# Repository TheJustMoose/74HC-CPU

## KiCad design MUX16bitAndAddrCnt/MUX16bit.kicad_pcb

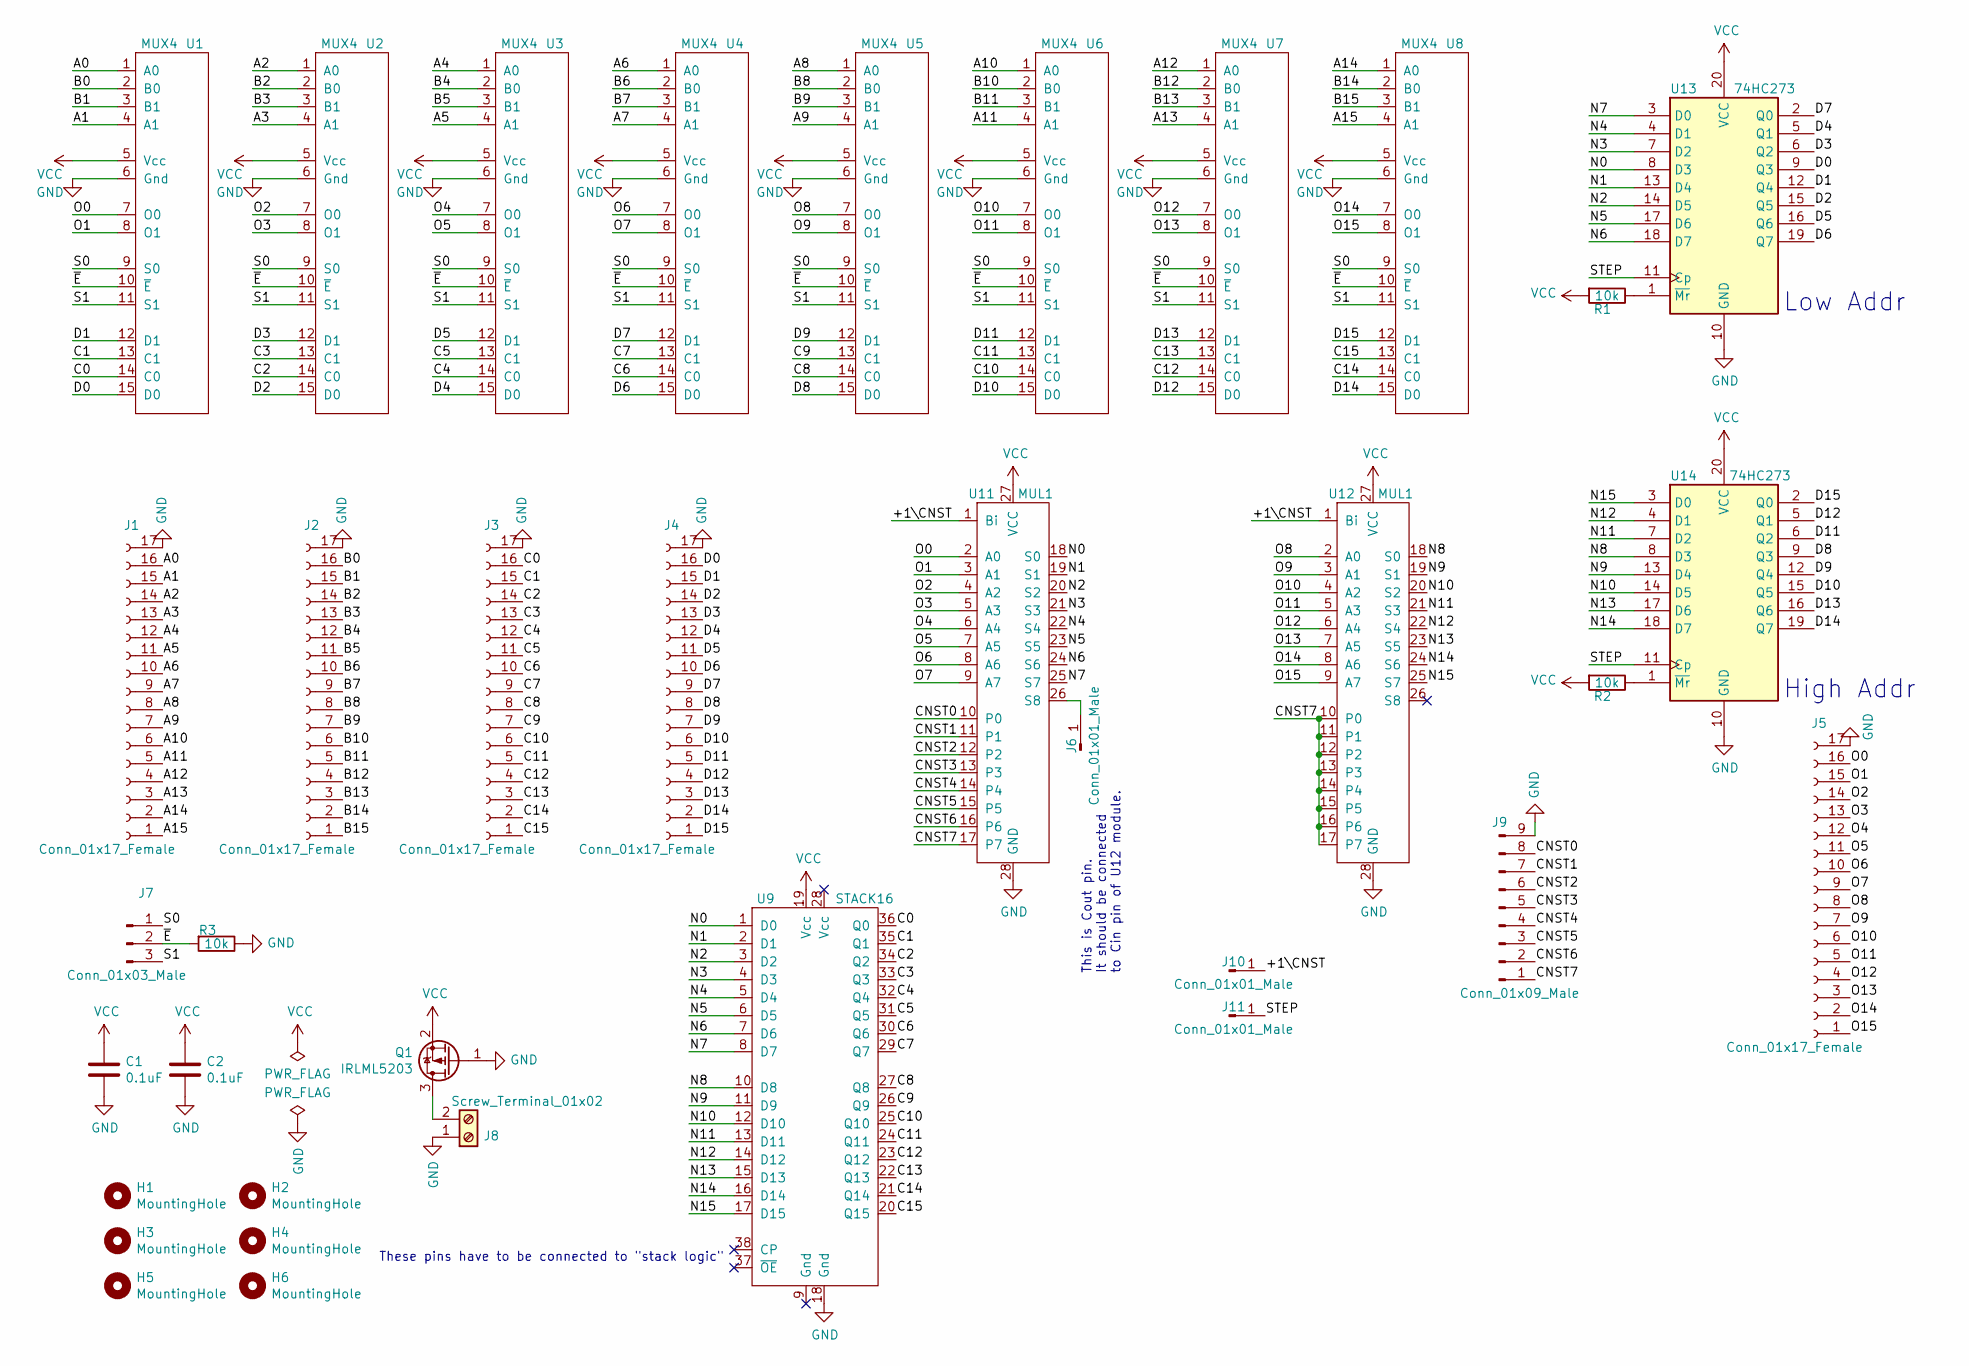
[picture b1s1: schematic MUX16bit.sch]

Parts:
C1, C2: 0.1uF; C_0805_2012Metric_Pad1.18x1.45mm_HandSolder
H1, H2, H3, H4, H5, H6: MountingHole; MountingHole_3.2mm_M3
J1, J2, J3, J4, J5: Conn_01x17_Female; PinSocket_1x17_P2.54mm_Vertical
J6, J10, J11: Conn_01x01_Male; PinHeader_1x01_P2.54mm_Vertical
J7: Conn_01x03_Male; PinHeader_1x03_P2.54mm_Vertical
J8: Screw_Terminal_01x02; TerminalBlock_Phoenix_PT-1,5-2-5.0-H_1x02_P5.00mm_Horizontal
J9: Conn_01x09_Male; PinHeader_1x09_P2.54mm_Vertical
Q1: IRLML5203; SOT-23
R1, R2, R3: 10k; R_0805_2012Metric_Pad1.20x1.40mm_HandSolder
U1, U2, U3, U4, U5, U6, U7, U8: MUX4; MUX1
U9: STACK16
U11, U12: MUL1
U13, U14: 74HC273; DIP-20_W7.62mm

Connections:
/+1\CNST: J10.1, U11.1 (Bi), U12.1 (Bi)
/A0: J1.16, U1.1 (A0)
/A1: J1.15, U1.4 (A1)
/A2: J1.14, U2.1 (A0)
/A3: J1.13, U2.4 (A1)
/A4: J1.12, U3.1 (A0)
/A5: J1.11, U3.4 (A1)
/A6: J1.10, U4.1 (A0)
/A7: J1.9, U4.4 (A1)
/A8: J1.8, U5.1 (A0)
/A9: J1.7, U5.4 (A1)
/A10: J1.6, U6.1 (A0)
/A11: J1.5, U6.4 (A1)
/A12: J1.4, U7.1 (A0)
/A13: J1.3, U7.4 (A1)
/A14: J1.2, U8.1 (A0)
/A15: J1.1, U8.4 (A1)
/B0: J2.16, U1.2 (B0)
/B1: J2.15, U1.3 (B1)
/B2: J2.14, U2.2 (B0)
/B3: J2.13, U2.3 (B1)
/B4: J2.12, U3.2 (B0)
/B5: J2.11, U3.3 (B1)
/B6: J2.10, U4.2 (B0)
/B7: J2.9, U4.3 (B1)
/B8: J2.8, U5.2 (B0)
/B9: J2.7, U5.3 (B1)
/B10: J2.6, U6.2 (B0)
/B11: J2.5, U6.3 (B1)
/B12: J2.4, U7.2 (B0)
/B13: J2.3, U7.3 (B1)
/B14: J2.2, U8.2 (B0)
/B15: J2.1, U8.3 (B1)
/C0: J3.16, U1.14 (C0), U9.36 (Q0)
/C1: J3.15, U1.13 (C1), U9.35 (Q1)
/C2: J3.14, U2.14 (C0), U9.34 (Q2)
/C3: J3.13, U2.13 (C1), U9.33 (Q3)
/C4: J3.12, U3.14 (C0), U9.32 (Q4)
/C5: J3.11, U3.13 (C1), U9.31 (Q5)
/C6: J3.10, U4.14 (C0), U9.30 (Q6)
/C7: J3.9, U4.13 (C1), U9.29 (Q7)
/C8: J3.8, U5.14 (C0), U9.27 (Q8)
/C9: J3.7, U5.13 (C1), U9.26 (Q9)
/C10: J3.6, U6.14 (C0), U9.25 (Q10)
/C11: J3.5, U6.13 (C1), U9.24 (Q11)
/C12: J3.4, U7.14 (C0), U9.23 (Q12)
/C13: J3.3, U7.13 (C1), U9.22 (Q13)
/C14: J3.2, U8.14 (C0), U9.21 (Q14)
/C15: J3.1, U8.13 (C1), U9.20 (Q15)
/CNST0: J9.8, U11.10 (P0)
/CNST1: J9.7, U11.11 (P1)
/CNST2: J9.6, U11.12 (P2)
/CNST3: J9.5, U11.13 (P3)
/CNST4: J9.4, U11.14 (P4)
/CNST5: J9.3, U11.15 (P5)
/CNST6: J9.2, U11.16 (P6)
/CNST7: J9.1, U11.17 (P7), U12.10 (P0), U12.11 (P1), U12.12 (P2), U12.13 (P3), U12.14 (P4), U12.15 (P5), U12.16 (P6), U12.17 (P7)
/D0: J4.16, U1.15 (D0), U13.9 (Q3)
/D1: J4.15, U1.12 (D1), U13.12 (Q4)
/D2: J4.14, U2.15 (D0), U13.15 (Q5)
/D3: J4.13, U2.12 (D1), U13.6 (Q2)
/D4: J4.12, U3.15 (D0), U13.5 (Q1)
/D5: J4.11, U3.12 (D1), U13.16 (Q6)
/D6: J4.10, U4.15 (D0), U13.19 (Q7)
/D7: J4.9, U4.12 (D1), U13.2 (Q0)
/D8: J4.8, U5.15 (D0), U14.9 (Q3)
/D9: J4.7, U5.12 (D1), U14.12 (Q4)
/D10: J4.6, U6.15 (D0), U14.15 (Q5)
/D11: J4.5, U6.12 (D1), U14.6 (Q2)
/D12: J4.4, U7.15 (D0), U14.5 (Q1)
/D13: J4.3, U7.12 (D1), U14.16 (Q6)
/D14: J4.2, U8.15 (D0), U14.19 (Q7)
/D15: J4.1, U8.12 (D1), U14.2 (Q0)
/N0: U9.1 (D0), U11.18 (S0), U13.8 (D3)
/N1: U9.2 (D1), U11.19 (S1), U13.13 (D4)
/N2: U9.3 (D2), U11.20 (S2), U13.14 (D5)
/N3: U9.4 (D3), U11.21 (S3), U13.7 (D2)
/N4: U9.5 (D4), U11.22 (S4), U13.4 (D1)
/N5: U9.6 (D5), U11.23 (S5), U13.17 (D6)
/N6: U9.7 (D6), U11.24 (S6), U13.18 (D7)
/N7: U9.8 (D7), U11.25 (S7), U13.3 (D0)
/N8: U9.10 (D8), U12.18 (S0), U14.8 (D3)
/N9: U9.11 (D9), U12.19 (S1), U14.13 (D4)
/N10: U9.12 (D10), U12.20 (S2), U14.14 (D5)
/N11: U9.13 (D11), U12.21 (S3), U14.7 (D2)
/N12: U9.14 (D12), U12.22 (S4), U14.4 (D1)
/N13: U9.15 (D13), U12.23 (S5), U14.17 (D6)
/N14: U9.16 (D14), U12.24 (S6), U14.18 (D7)
/N15: U9.17 (D15), U12.25 (S7), U14.3 (D0)
/O0: J5.16, U1.7 (O0), U11.2 (A0)
/O1: J5.15, U1.8 (O1), U11.3 (A1)
/O2: J5.14, U2.7 (O0), U11.4 (A2)
/O3: J5.13, U2.8 (O1), U11.5 (A3)
/O4: J5.12, U3.7 (O0), U11.6 (A4)
/O5: J5.11, U3.8 (O1), U11.7 (A5)
/O6: J5.10, U4.7 (O0), U11.8 (A6)
/O7: J5.9, U4.8 (O1), U11.9 (A7)
/O8: J5.8, U5.7 (O0), U12.2 (A0)
/O9: J5.7, U5.8 (O1), U12.3 (A1)
/O10: J5.6, U6.7 (O0), U12.4 (A2)
/O11: J5.5, U6.8 (O1), U12.5 (A3)
/O12: J5.4, U7.7 (O0), U12.6 (A4)
/O13: J5.3, U7.8 (O1), U12.7 (A5)
/O14: J5.2, U8.7 (O0), U12.8 (A6)
/O15: J5.1, U8.8 (O1), U12.9 (A7)
/S0: J7.1, U1.9 (S0), U2.9 (S0), U3.9 (S0), U4.9 (S0), U5.9 (S0), U6.9 (S0), U7.9 (S0), U8.9 (S0)
/S1: J7.3, U1.11 (S1), U2.11 (S1), U3.11 (S1), U4.11 (S1), U5.11 (S1), U6.11 (S1), U7.11 (S1), U8.11 (S1)
/STEP: J11.1, U13.11 (Cp), U14.11 (Cp)
/~E: J7.2, R3.2, U1.10 (~E), U2.10 (~E), U3.10 (~E), U4.10 (~E), U5.10 (~E), U6.10 (~E), U7.10 (~E), U8.10 (~E)
GND: C1.2, C2.2, J1.17, J2.17, J3.17, J4.17, J5.17, J8.1, J9.9, Q1.1 (G), R3.1, U1.6 (Gnd), U2.6 (Gnd), U3.6 (Gnd), U4.6 (Gnd), U5.6 (Gnd), U6.6 (Gnd), U7.6 (Gnd), U8.6 (Gnd), U9.18 (Gnd), U11.28 (GND), U12.28 (GND), U13.10 (GND), U14.10 (GND)
unnamed: J6.1, U11.26 (S8)
unnamed: J8.2, Q1.3 (D)
unnamed: R1.1, U13.1 (~Mr)
unnamed: R2.1, U14.1 (~Mr)
VCC: C1.1, C2.1, Q1.2 (S), R1.2, R2.2, U1.5 (Vcc), U2.5 (Vcc), U3.5 (Vcc), U4.5 (Vcc), U5.5 (Vcc), U6.5 (Vcc), U7.5 (Vcc), U8.5 (Vcc), U9.19 (Vcc), U11.27 (VCC), U12.27 (VCC), U13.20 (VCC), U14.20 (VCC)

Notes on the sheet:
Low Addr
High Addr
This is Cout pin. It should be connected to Cin pin of U12 module.
These pins have to be connected to "stack logic"

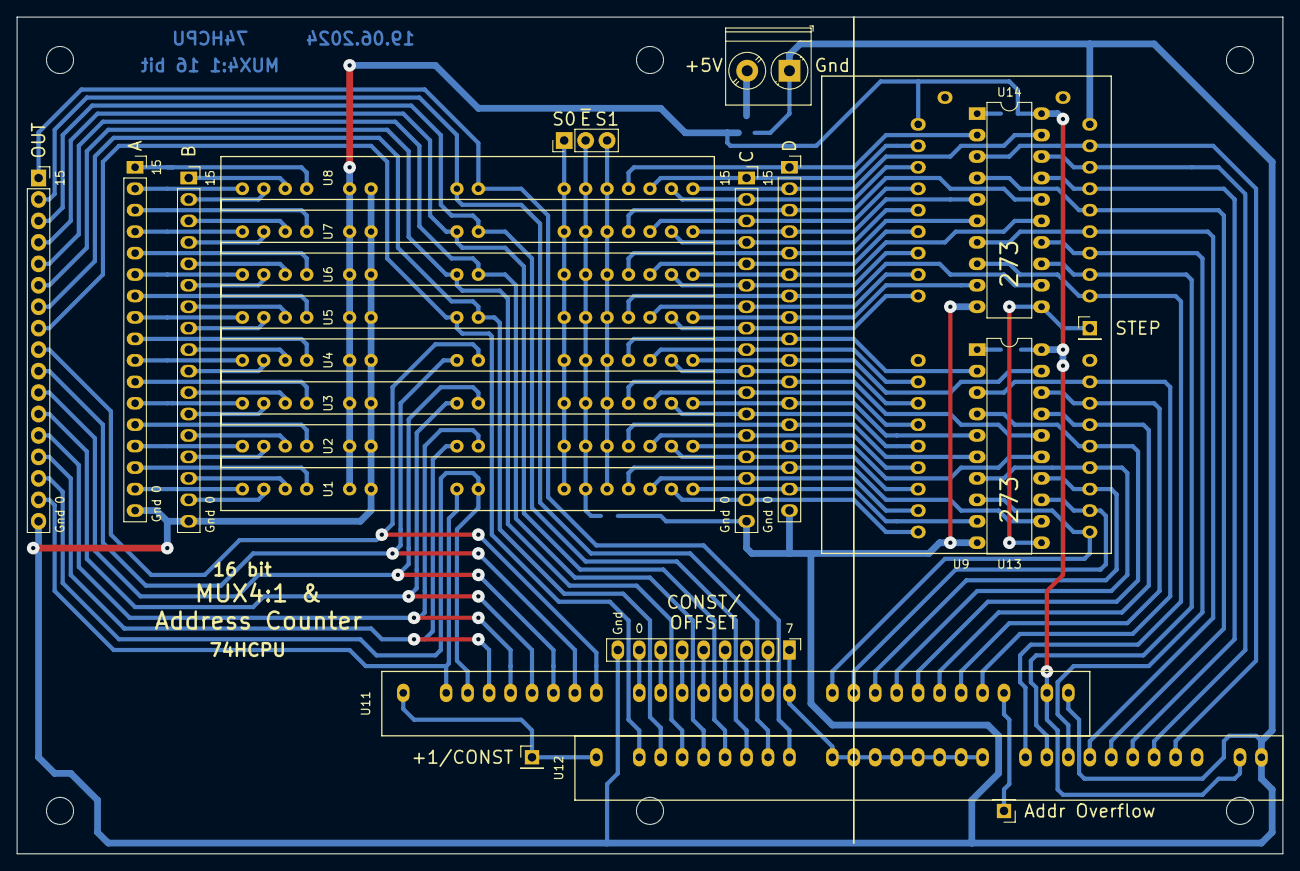
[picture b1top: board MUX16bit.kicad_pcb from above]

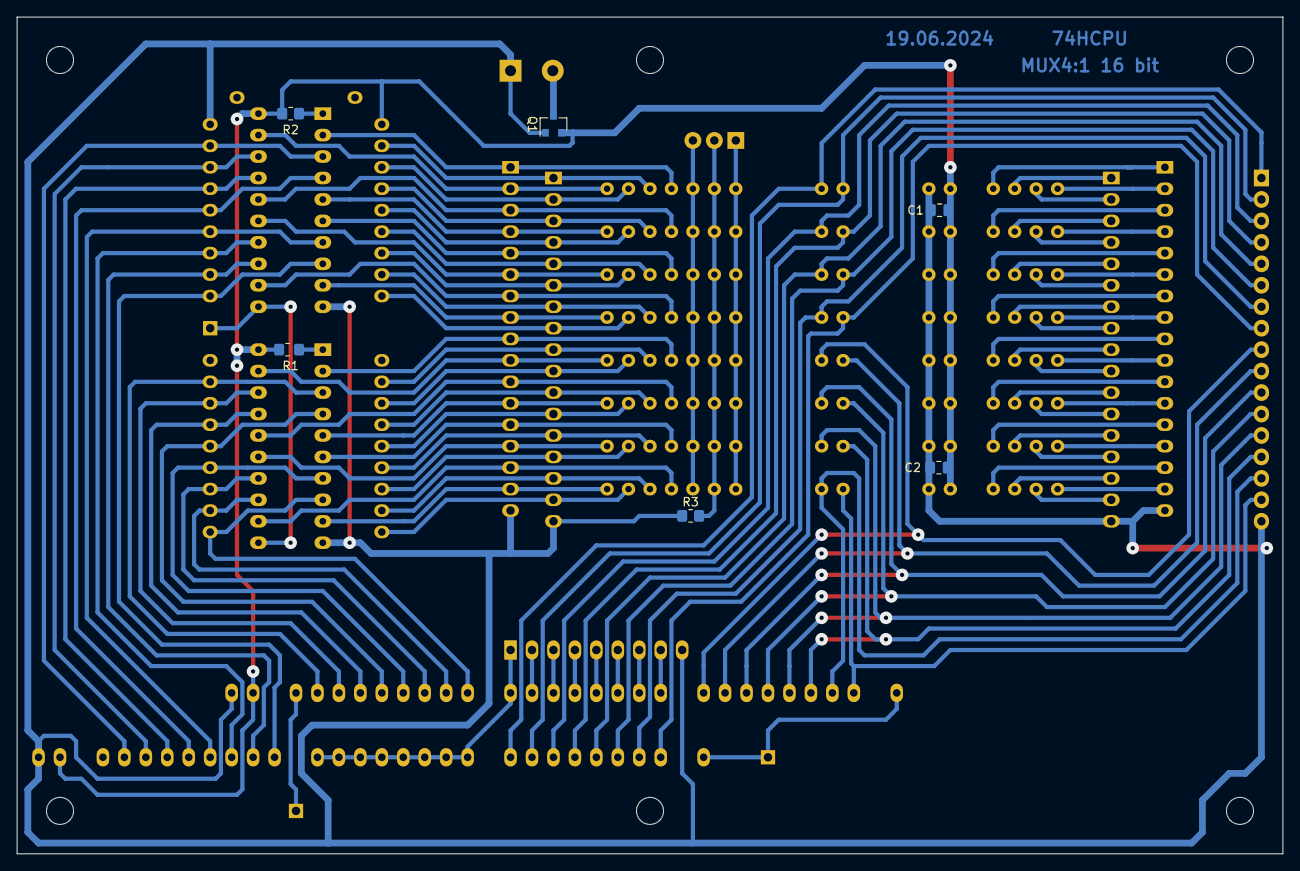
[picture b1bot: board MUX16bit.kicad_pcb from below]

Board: 2 copper layers, 149.9 x 99.1 mm, 36 parts (6 on the bottom side), 115 nets.

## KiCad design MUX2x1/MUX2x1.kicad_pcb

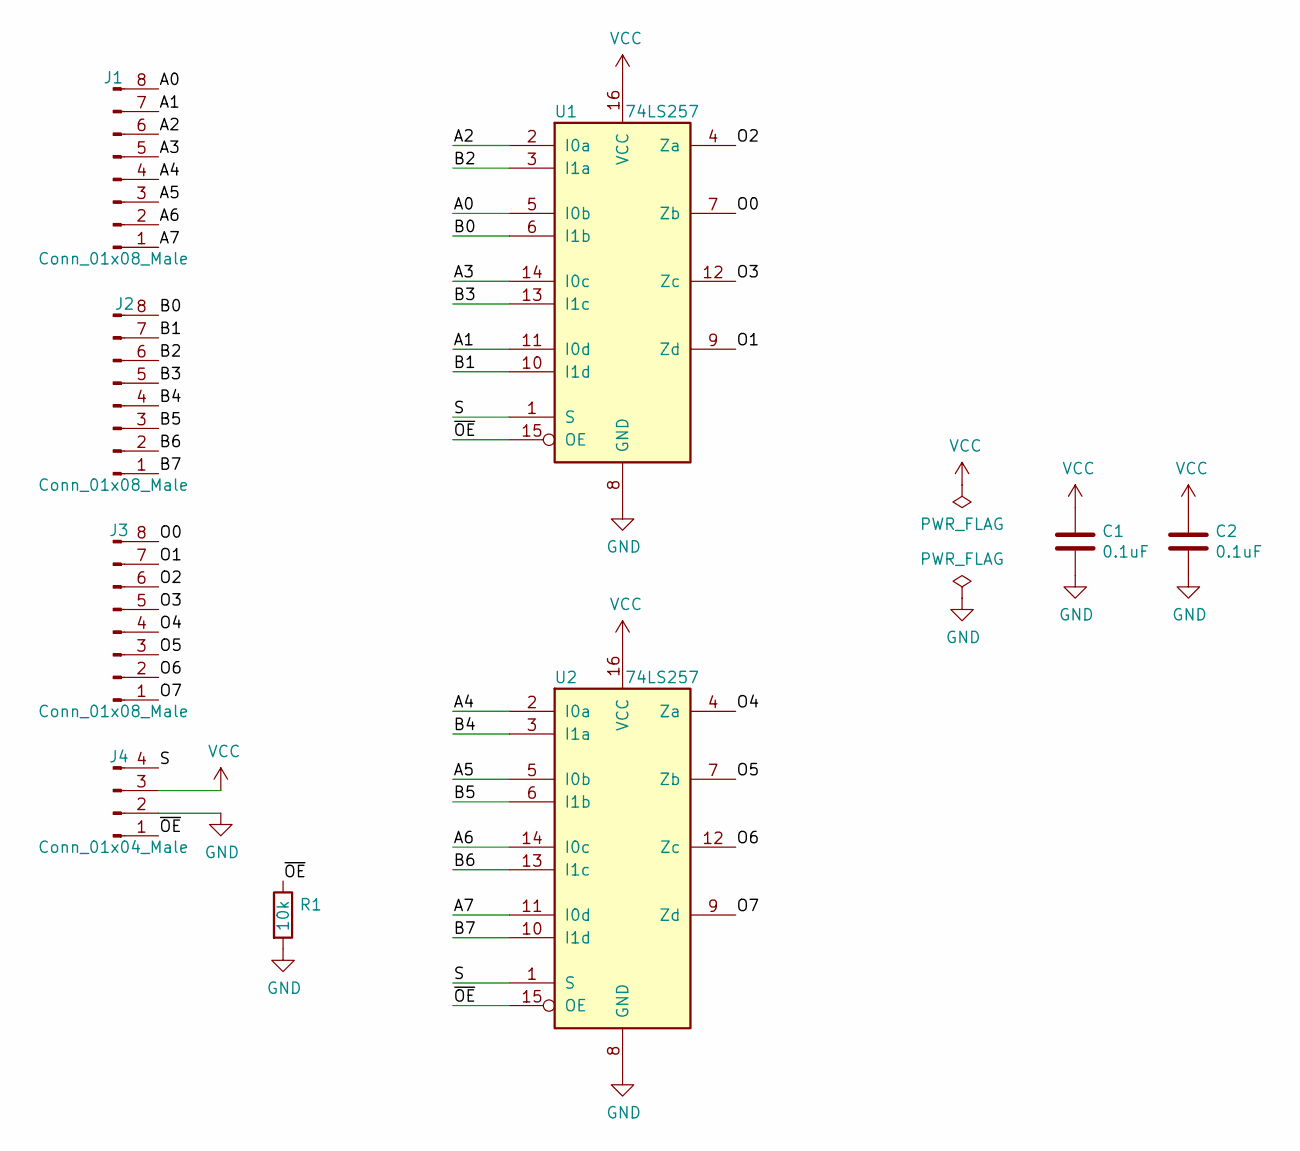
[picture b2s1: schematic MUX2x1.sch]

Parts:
C1, C2: 0.1uF; C_0805_2012Metric_Pad1.18x1.45mm_HandSolder
J1, J2, J3: Conn_01x08_Male; PinHeader_1x08_P2.54mm_Horizontal
J4: Conn_01x04_Male; PinHeader_1x04_P2.54mm_Horizontal
R1: 10k; R_0805_2012Metric_Pad1.20x1.40mm_HandSolder
U1, U2: 74LS257; DIP-16_W7.62mm_Socket

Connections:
/A0: J1.8, U1.5 (I0b)
/A1: J1.7, U1.11 (I0d)
/A2: J1.6, U1.2 (I0a)
/A3: J1.5, U1.14 (I0c)
/A4: J1.4, U2.2 (I0a)
/A5: J1.3, U2.5 (I0b)
/A6: J1.2, U2.14 (I0c)
/A7: J1.1, U2.11 (I0d)
/B0: J2.8, U1.6 (I1b)
/B1: J2.7, U1.10 (I1d)
/B2: J2.6, U1.3 (I1a)
/B3: J2.5, U1.13 (I1c)
/B4: J2.4, U2.3 (I1a)
/B5: J2.3, U2.6 (I1b)
/B6: J2.2, U2.13 (I1c)
/B7: J2.1, U2.10 (I1d)
/O0: J3.8, U1.7 (Zb)
/O1: J3.7, U1.9 (Zd)
/O2: J3.6, U1.4 (Za)
/O3: J3.5, U1.12 (Zc)
/O4: J3.4, U2.4 (Za)
/O5: J3.3, U2.7 (Zb)
/O6: J3.2, U2.12 (Zc)
/O7: J3.1, U2.9 (Zd)
/S: J4.4, U1.1 (S), U2.1 (S)
/~OE: J4.1, R1.1, U1.15 (OE), U2.15 (OE)
GND: C1.2, C2.2, J4.2, R1.2, U1.8 (GND), U2.8 (GND)
VCC: C1.1, C2.1, J4.3, U1.16 (VCC), U2.16 (VCC)

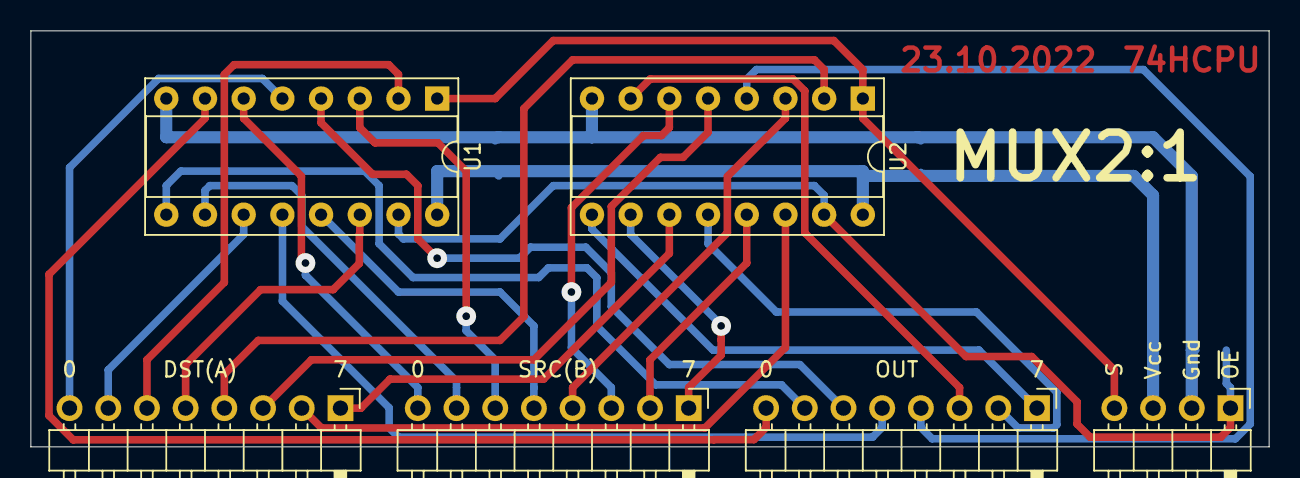
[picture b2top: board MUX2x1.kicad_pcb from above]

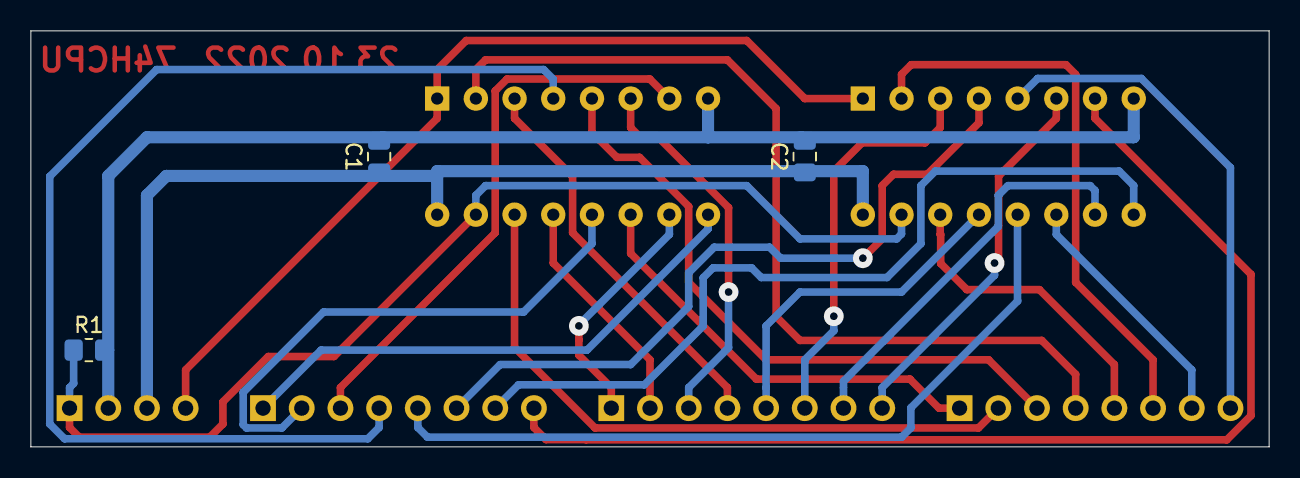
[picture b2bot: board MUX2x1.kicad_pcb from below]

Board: 2 copper layers, 81.3 x 27.3 mm, 9 parts (3 on the bottom side), 28 nets.

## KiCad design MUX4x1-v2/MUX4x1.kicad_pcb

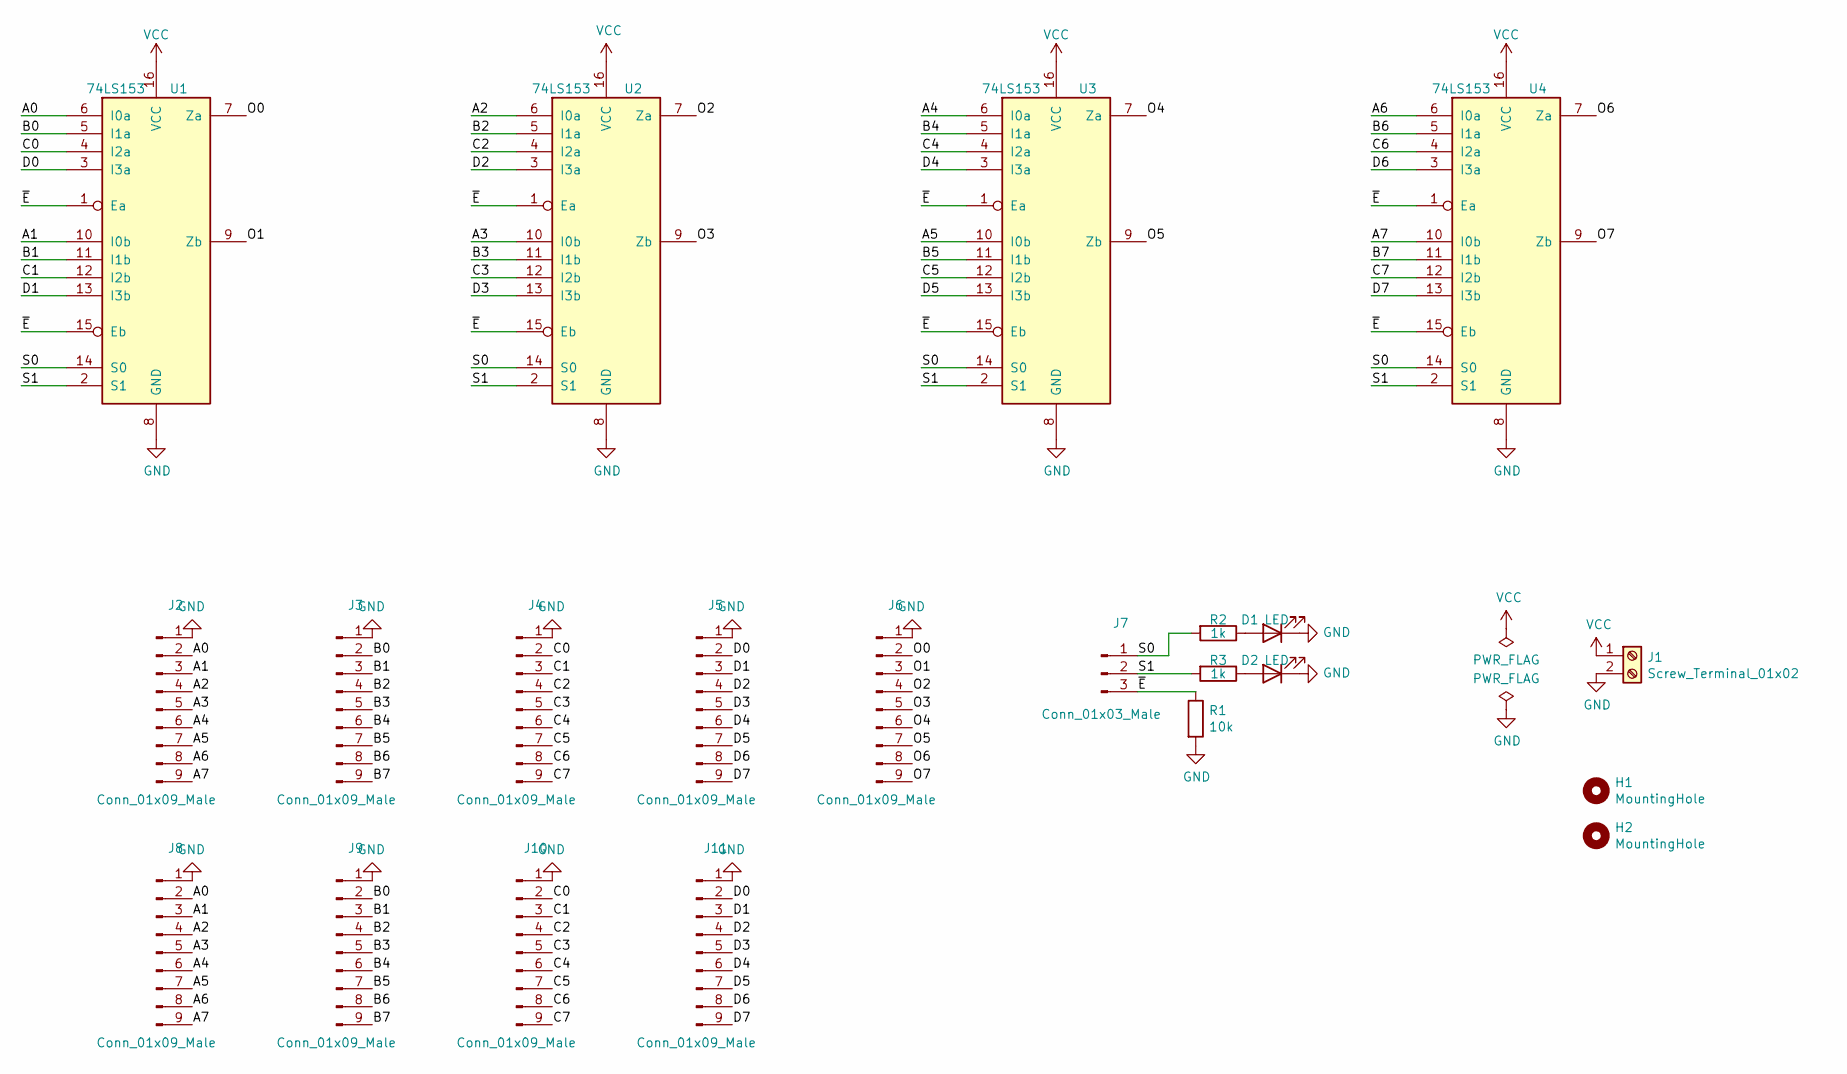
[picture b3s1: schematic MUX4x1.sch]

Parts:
D1, D2: LED; LED_0805_2012Metric_Pad1.15x1.40mm_HandSolder
H1, H2: MountingHole; MountingHole_3.2mm_M3
J1: Screw_Terminal_01x02; TerminalBlock_Phoenix_PT-1,5-2-5.0-H_1x02_P5.00mm_Horizontal
J2, J3, J4, J5, J6, J8, J9, J10, J11: Conn_01x09_Male; PinHeader_1x09_P2.54mm_Vertical
J7: Conn_01x03_Male; PinHeader_1x03_P2.54mm_Vertical
R1: 10k; R_0805_2012Metric_Pad1.20x1.40mm_HandSolder
R2, R3: 1k; R_0805_2012Metric_Pad1.20x1.40mm_HandSolder
U1, U2, U3, U4: 74LS153; DIP-16_W7.62mm_Socket

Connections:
/A0: J2.2, J8.2, U1.6 (I0a)
/A1: J2.3, J8.3, U1.10 (I0b)
/A2: J2.4, J8.4, U2.6 (I0a)
/A3: J2.5, J8.5, U2.10 (I0b)
/A4: J2.6, J8.6, U3.6 (I0a)
/A5: J2.7, J8.7, U3.10 (I0b)
/A6: J2.8, J8.8, U4.6 (I0a)
/A7: J2.9, J8.9, U4.10 (I0b)
/B0: J3.2, J9.2, U1.5 (I1a)
/B1: J3.3, J9.3, U1.11 (I1b)
/B2: J3.4, J9.4, U2.5 (I1a)
/B3: J3.5, J9.5, U2.11 (I1b)
/B4: J3.6, J9.6, U3.5 (I1a)
/B5: J3.7, J9.7, U3.11 (I1b)
/B6: J3.8, J9.8, U4.5 (I1a)
/B7: J3.9, J9.9, U4.11 (I1b)
/C0: J4.2, J10.2, U1.4 (I2a)
/C1: J4.3, J10.3, U1.12 (I2b)
/C2: J4.4, J10.4, U2.4 (I2a)
/C3: J4.5, J10.5, U2.12 (I2b)
/C4: J4.6, J10.6, U3.4 (I2a)
/C5: J4.7, J10.7, U3.12 (I2b)
/C6: J4.8, J10.8, U4.4 (I2a)
/C7: J4.9, J10.9, U4.12 (I2b)
/D0: J5.2, J11.2, U1.3 (I3a)
/D1: J5.3, J11.3, U1.13 (I3b)
/D2: J5.4, J11.4, U2.3 (I3a)
/D3: J5.5, J11.5, U2.13 (I3b)
/D4: J5.6, J11.6, U3.3 (I3a)
/D5: J5.7, J11.7, U3.13 (I3b)
/D6: J5.8, J11.8, U4.3 (I3a)
/D7: J5.9, J11.9, U4.13 (I3b)
/O0: J6.2, U1.7 (Za); also elsewhere on the board
/O1: J6.3, U1.9 (Zb); also elsewhere on the board
/O2: J6.4, U2.7 (Za); also elsewhere on the board
/O3: J6.5, U2.9 (Zb); also elsewhere on the board
/O4: J6.6, U3.7 (Za); also elsewhere on the board
/O5: J6.7, U3.9 (Zb); also elsewhere on the board
/O6: J6.8, U4.7 (Za); also elsewhere on the board
/O7: J6.9, U4.9 (Zb); also elsewhere on the board
/S0: J7.1, R2.2, U1.14 (S0), U2.14 (S0), U3.14 (S0), U4.14 (S0)
/S1: J7.2, R3.2, U1.2 (S1), U2.2 (S1), U3.2 (S1), U4.2 (S1)
/~E: J7.3, R1.1, U1.1 (Ea), U1.15 (Eb), U2.1 (Ea), U2.15 (Eb), U3.1 (Ea), U3.15 (Eb), U4.1 (Ea), U4.15 (Eb)
GND: D1.1 (K), D2.1 (K), J1.2, J2.1, J3.1, J4.1, J5.1, J6.1, J8.1, J9.1, J10.1, J11.1, R1.2, U1.8 (GND), U2.8 (GND), U3.8 (GND), U4.8 (GND); also elsewhere on the board
unnamed: D1.2 (A), R2.1
unnamed: D2.2 (A), R3.1
VCC: J1.1, U1.16 (VCC), U2.16 (VCC), U3.16 (VCC), U4.16 (VCC)

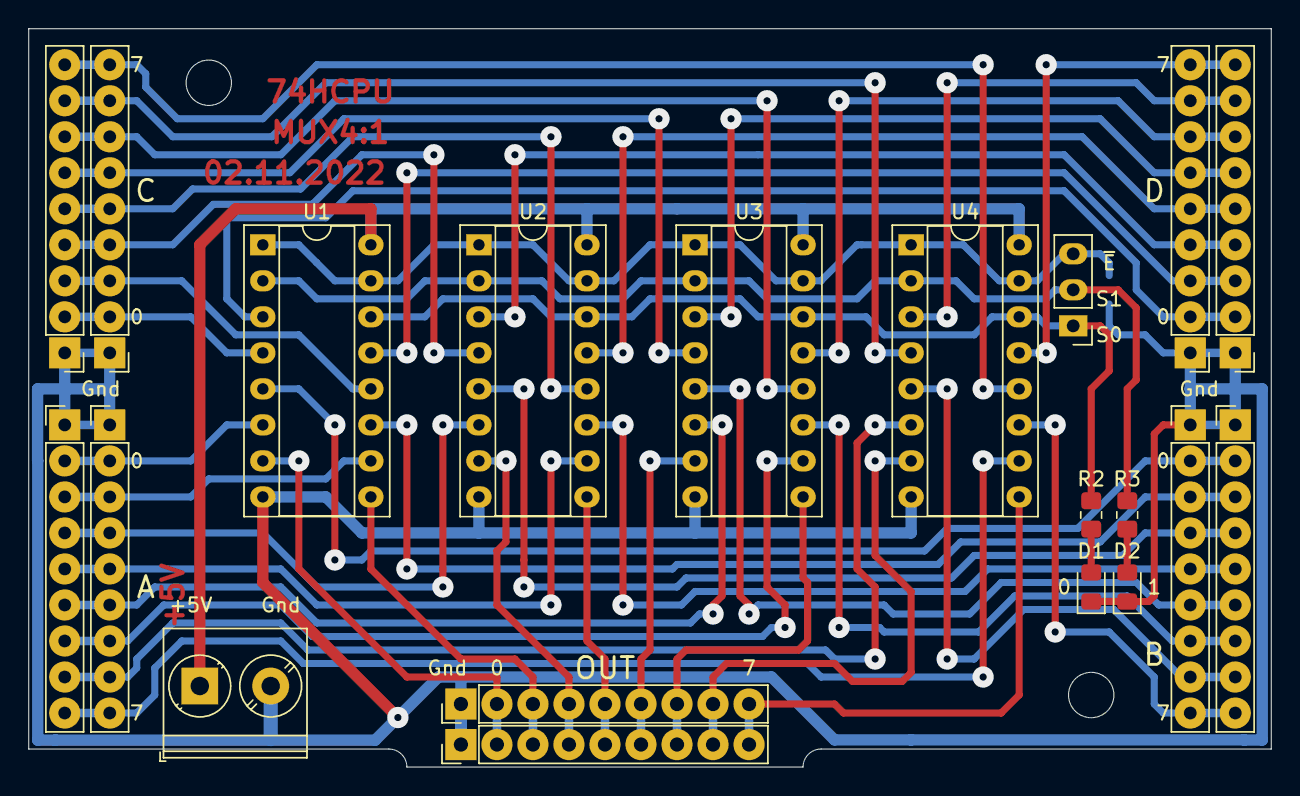
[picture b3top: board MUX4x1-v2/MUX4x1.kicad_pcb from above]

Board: 2 copper layers, 87.6 x 52.1 mm, 23 parts (1 on the bottom side), 47 nets.

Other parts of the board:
J12: Conn_01x09_Male; PinHeader_1x09_P2.54mm_Vertical

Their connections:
/O0: J12.2; also elsewhere on the board
/O1: J12.3; also elsewhere on the board
/O2: J12.4; also elsewhere on the board
/O3: J12.5; also elsewhere on the board
/O4: J12.6; also elsewhere on the board
/O5: J12.7; also elsewhere on the board
/O6: J12.8; also elsewhere on the board
/O7: J12.9; also elsewhere on the board
GND: J12.1; also elsewhere on the board

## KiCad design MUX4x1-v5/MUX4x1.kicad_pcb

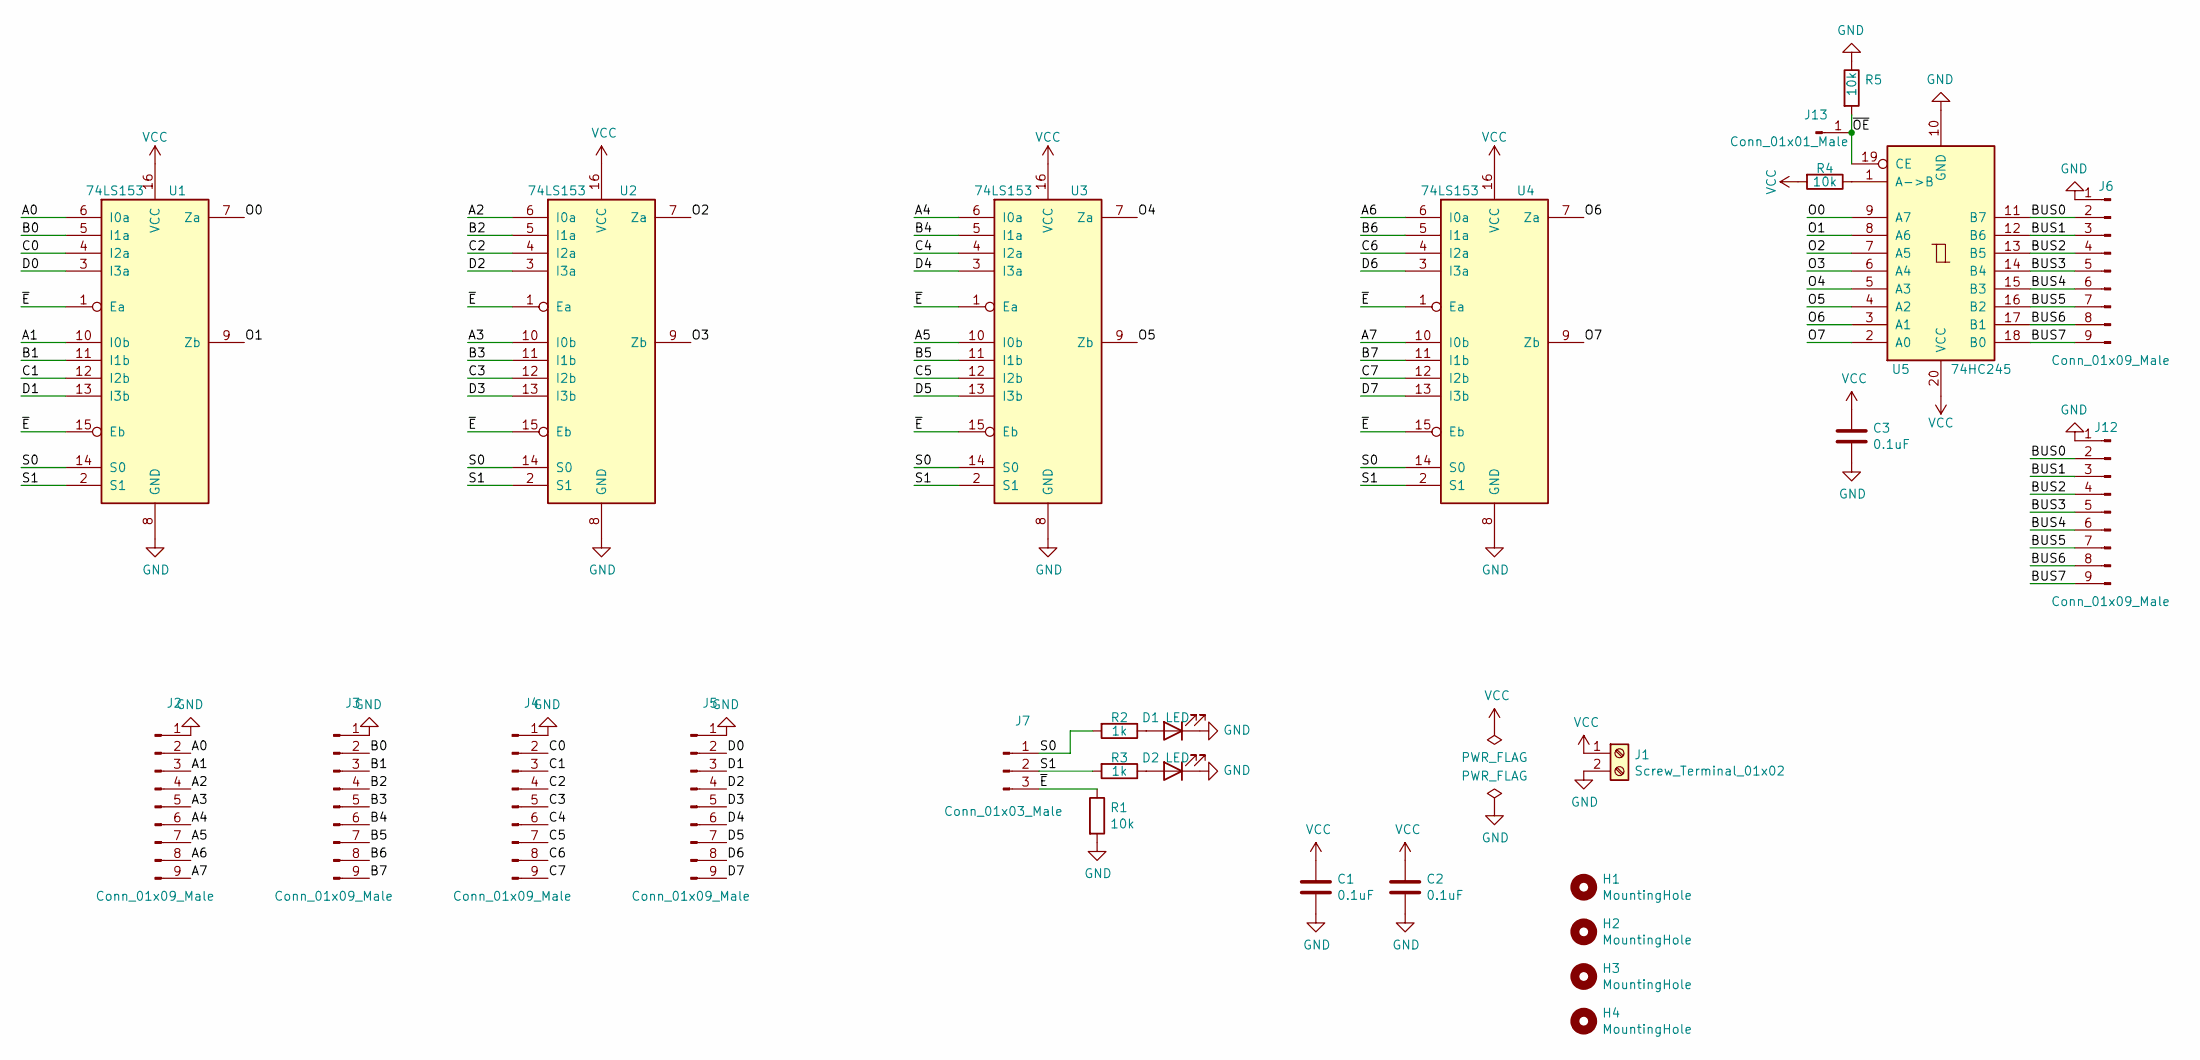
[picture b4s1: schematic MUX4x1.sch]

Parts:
C1, C2, C3: 0.1uF; C_0805_2012Metric_Pad1.18x1.45mm_HandSolder
D1, D2: LED; LED_0805_2012Metric_Pad1.15x1.40mm_HandSolder
H1, H2, H3, H4: MountingHole; MountingHole_3.2mm_M3
J1: Screw_Terminal_01x02; TerminalBlock_Phoenix_PT-1,5-2-5.0-H_1x02_P5.00mm_Horizontal
J2, J3, J4, J5, J6, J12: Conn_01x09_Male; PinHeader_1x09_P2.54mm_Vertical
J7: Conn_01x03_Male; PinHeader_1x03_P2.54mm_Vertical
J13: Conn_01x01_Male; PinHeader_1x01_P2.54mm_Vertical
R1, R4, R5: 10k; R_0805_2012Metric_Pad1.20x1.40mm_HandSolder
R2, R3: 1k; R_0805_2012Metric_Pad1.20x1.40mm_HandSolder
U1, U2, U3, U4: 74LS153; DIP-16_W7.62mm_Socket
U5: 74HC245; DIP-20_W7.62mm_Socket

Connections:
/A0: J2.2, U1.6 (I0a)
/A1: J2.3, U1.10 (I0b)
/A2: J2.4, U2.6 (I0a)
/A3: J2.5, U2.10 (I0b)
/A4: J2.6, U3.6 (I0a)
/A5: J2.7, U3.10 (I0b)
/A6: J2.8, U4.6 (I0a)
/A7: J2.9, U4.10 (I0b)
/B0: J3.2, U1.5 (I1a)
/B1: J3.3, U1.11 (I1b)
/B2: J3.4, U2.5 (I1a)
/B3: J3.5, U2.11 (I1b)
/B4: J3.6, U3.5 (I1a)
/B5: J3.7, U3.11 (I1b)
/B6: J3.8, U4.5 (I1a)
/B7: J3.9, U4.11 (I1b)
/BUS0: J6.2, J12.2, U5.11 (B7)
/BUS1: J6.3, J12.3, U5.12 (B6)
/BUS2: J6.4, J12.4, U5.13 (B5)
/BUS3: J6.5, J12.5, U5.14 (B4)
/BUS4: J6.6, J12.6, U5.15 (B3)
/BUS5: J6.7, J12.7, U5.16 (B2)
/BUS6: J6.8, J12.8, U5.17 (B1)
/BUS7: J6.9, J12.9, U5.18 (B0)
/C0: J4.2, U1.4 (I2a)
/C1: J4.3, U1.12 (I2b)
/C2: J4.4, U2.4 (I2a)
/C3: J4.5, U2.12 (I2b)
/C4: J4.6, U3.4 (I2a)
/C5: J4.7, U3.12 (I2b)
/C6: J4.8, U4.4 (I2a)
/C7: J4.9, U4.12 (I2b)
/D0: J5.2, U1.3 (I3a)
/D1: J5.3, U1.13 (I3b)
/D2: J5.4, U2.3 (I3a)
/D3: J5.5, U2.13 (I3b)
/D4: J5.6, U3.3 (I3a)
/D5: J5.7, U3.13 (I3b)
/D6: J5.8, U4.3 (I3a)
/D7: J5.9, U4.13 (I3b)
/O0: U1.7 (Za), U5.9 (A7)
/O1: U1.9 (Zb), U5.8 (A6)
/O2: U2.7 (Za), U5.7 (A5)
/O3: U2.9 (Zb), U5.6 (A4)
/O4: U3.7 (Za), U5.5 (A3)
/O5: U3.9 (Zb), U5.4 (A2)
/O6: U4.7 (Za), U5.3 (A1)
/O7: U4.9 (Zb), U5.2 (A0)
/~E: J7.3, R1.1, U1.1 (Ea), U1.15 (Eb), U2.1 (Ea), U2.15 (Eb), U3.1 (Ea), U3.15 (Eb), U4.1 (Ea), U4.15 (Eb)
/~OE: J13.1, R5.2, U5.19 (CE)
GND: C1.2, C2.2, C3.2, D1.1 (K), D2.1 (K), J1.2, J2.1, J3.1, J4.1, J5.1, J6.1, J12.1, R1.2, R5.1, U1.8 (GND), U2.8 (GND), U3.8 (GND), U4.8 (GND), U5.10 (GND); also elsewhere on the board
unnamed: D1.2 (A), R2.1
unnamed: D2.2 (A), R3.1
unnamed: R4.1, U5.1 (A->B)
VCC: C1.1, C2.1, C3.1, J1.1, R4.2, U1.16 (VCC), U2.16 (VCC), U3.16 (VCC), U4.16 (VCC), U5.20 (VCC); also elsewhere on the board

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
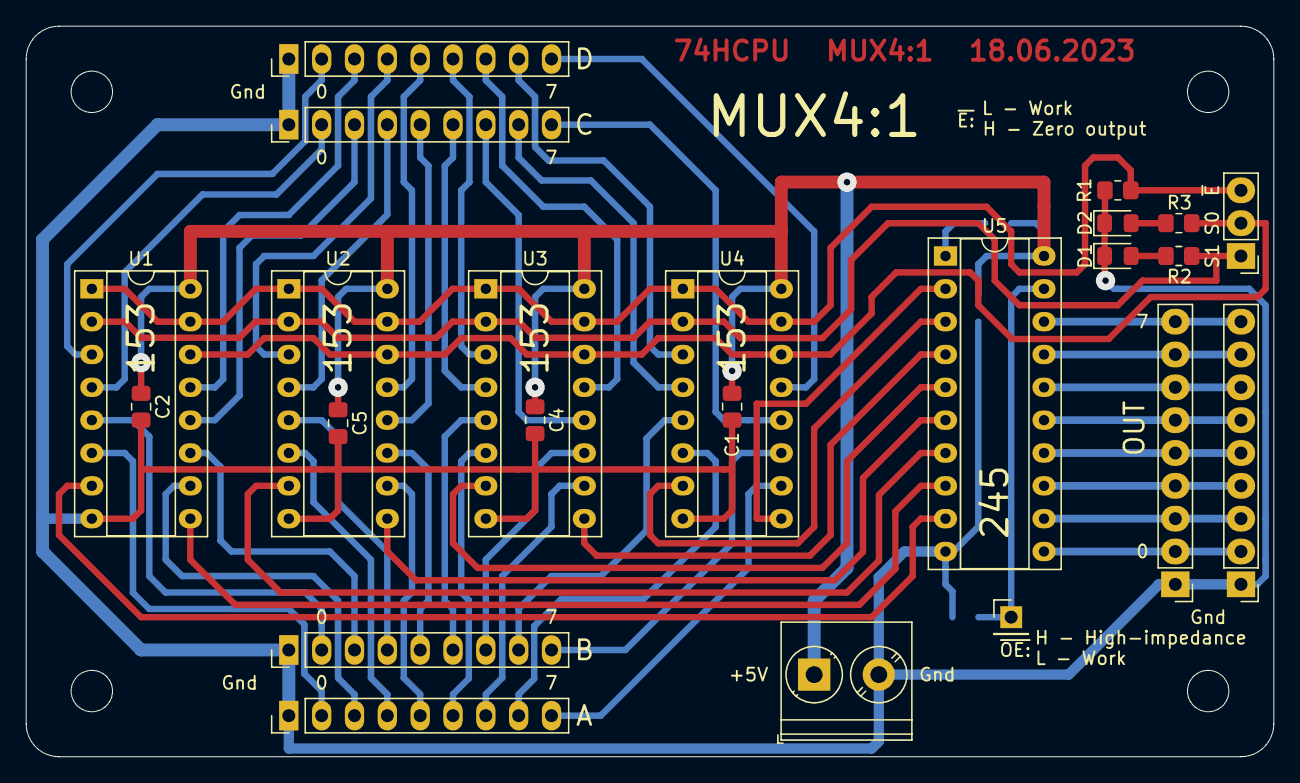
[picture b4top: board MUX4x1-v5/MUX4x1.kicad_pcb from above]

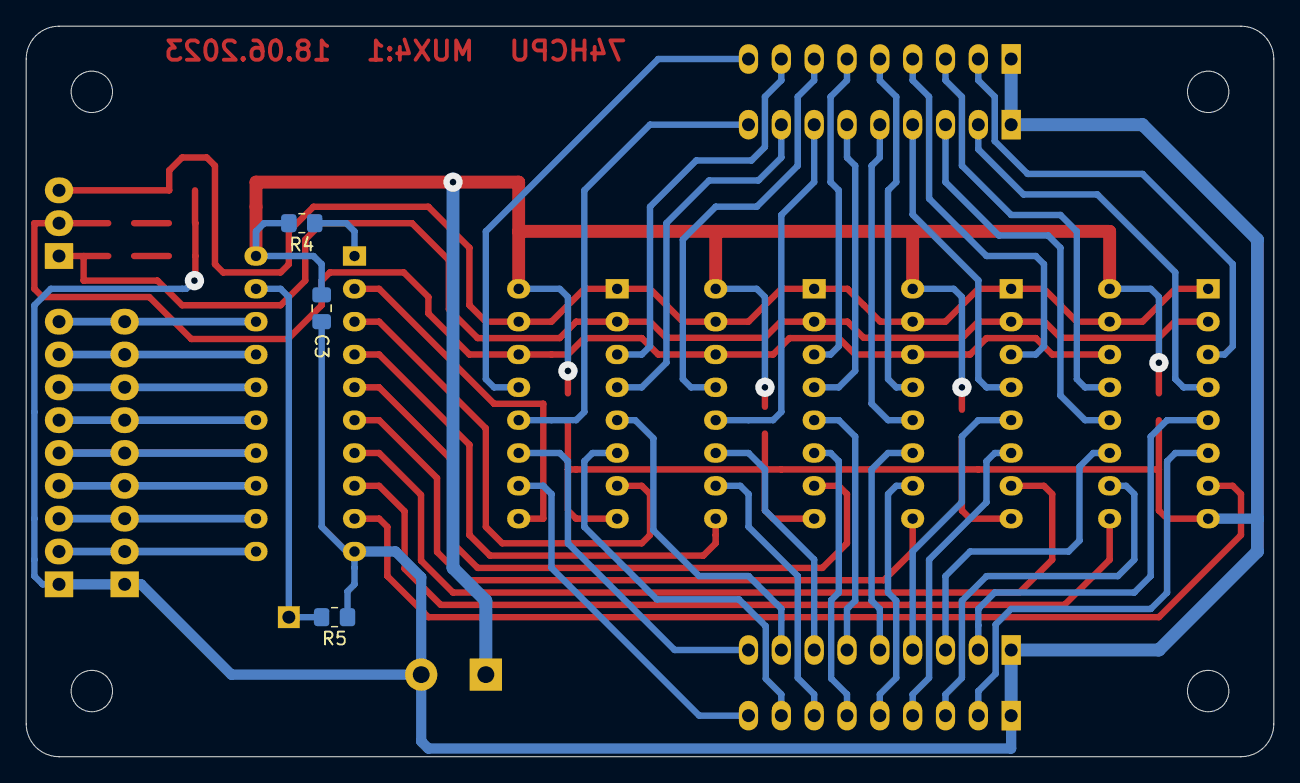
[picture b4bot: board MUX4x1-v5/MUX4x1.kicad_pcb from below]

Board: 2 copper layers, 96.5 x 56.5 mm, 30 parts (3 on the bottom side), 57 nets.

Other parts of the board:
C4, C5: 0.1uF; C_0805_2012Metric_Pad1.18x1.45mm_HandSolder

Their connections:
GND: C4.2, C5.2; also elsewhere on the board
VCC: C4.1, C5.1; also elsewhere on the board
